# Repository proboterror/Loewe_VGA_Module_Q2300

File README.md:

# Loewe TVs Q2300 VGA Module
Recreation of VGA module PCB for Loewe TVs with Q2300 chassis.<br>
[Loewe Q2400/Q2500 Chassis VGA Module](https://github.com/proboterror/Loewe_VGA_Module_Q2500)

Project based on schematic from [Loewe Q2300 Chassis Service Manual](doc/loewe_chassis_q2300.pdf)

Schematic and PCB recreated from the scratch in KiCad and verified with Desing/Electrical Rules Checker tools.<br>

Original schematic from [Loewe Q2300 Chassis Service Manual](doc/loewe_chassis_q2300.pdf):

Recreated schematic and PCB:

VGA connector breakout board:

## Bill of materials
|Reference|Value|Footprint|Qty|
|-----|-----|-----|-----|
|C3,C5,C7|4.7u|Capacitor_SMD:CP_Elec_6.3x5.4|3|
|C4,C6,C8,C14|100n|0805|4|
|C9,C26|22n|0805|2|
|C10|1u|Capacitor_Tantalum_SMD<br>CP_EIA-3216-18_Kemet-A_Pad1.58x1.35mm_HandSolder|1|
|C13|100u|Capacitor_SMD:CP_Elec_6.3x5.7|1|
|C15,C18,C19,C20,C21,C22,C24|10p|0805|7|
|C25,C28,C29|100p|0805|3|
|J1|VGA DSUB-15|DSUB-15-HD_Male_Horizontal_P2.29x1.98mm<br>EdgePinOffset3.03mm_MountingHolesOffset4.94mm|1|
|J2|JST XH 10 pin Horizontal|JST_XH_S10B-XH-A_1x10_P2.50mm_Horizontal|1|
|L1|4u7|Inductor_SMD:1206|1|
|Q1,Q2,Q3,Q4,Q5,Q6,Q10,Q14|BC847B|SOT-23|8|
|R1,R6,R13|75R|0805|3|
|R2,R5,R7,R10,R14,R18,R19,R26,R32|47K|0805|9|
|R3,R8,R15|22K|0805|3|
|R4,R9,R17,R33,R34|100R|0805|5|
|R22|10K|0805|1|
|R25,R31,R35,R40,R43|1K|0805|5|
|U1|74HCT86|SO-14_3.9x8.65mm_P1.27mm|1|
|W2|JST XH 10 pin Vertical|JST_XH_B10B-XH-A_1x10_P2.50mm_Vertical|1|
|W3|JST XH 10 pin Vertical|JST_XH_B10B-XH-A_1x10_P2.50mm_Vertical|1|

+Cables XH 10 pin 20 + 30~50 cm, connectors: same side

## Order boards from manufacturer
Project split to 2 PCBs which should be ordered separately.
Send "gerbers\Breakout Board" and "gerbers\Main Board" folders content packed to separate zip archives.

## Build Notes
L1 inductor can be replaced with 0R resistor or solder bridge.

Pay attention on cables connectors type: same direction or reverse direction.

## Install

<https://www.youtube.com/watch?v=7eVl5yn5JIE>:<br>
Select VGA input:<br>
@djcalle1975:
> On the Q23 you have to navigate to channel 196 and if no input is detected within 10 seconds the TV will default back to the last used channel.

VGA Geometry menu:<br>
@peteagas:
> If there is no VGA menu for you on a Q23 after installation and after enabling the option byte setting, press the "i" on the Loewe remote then go to select control level then simple control level set to "No". VGA geometry will now be available to use.

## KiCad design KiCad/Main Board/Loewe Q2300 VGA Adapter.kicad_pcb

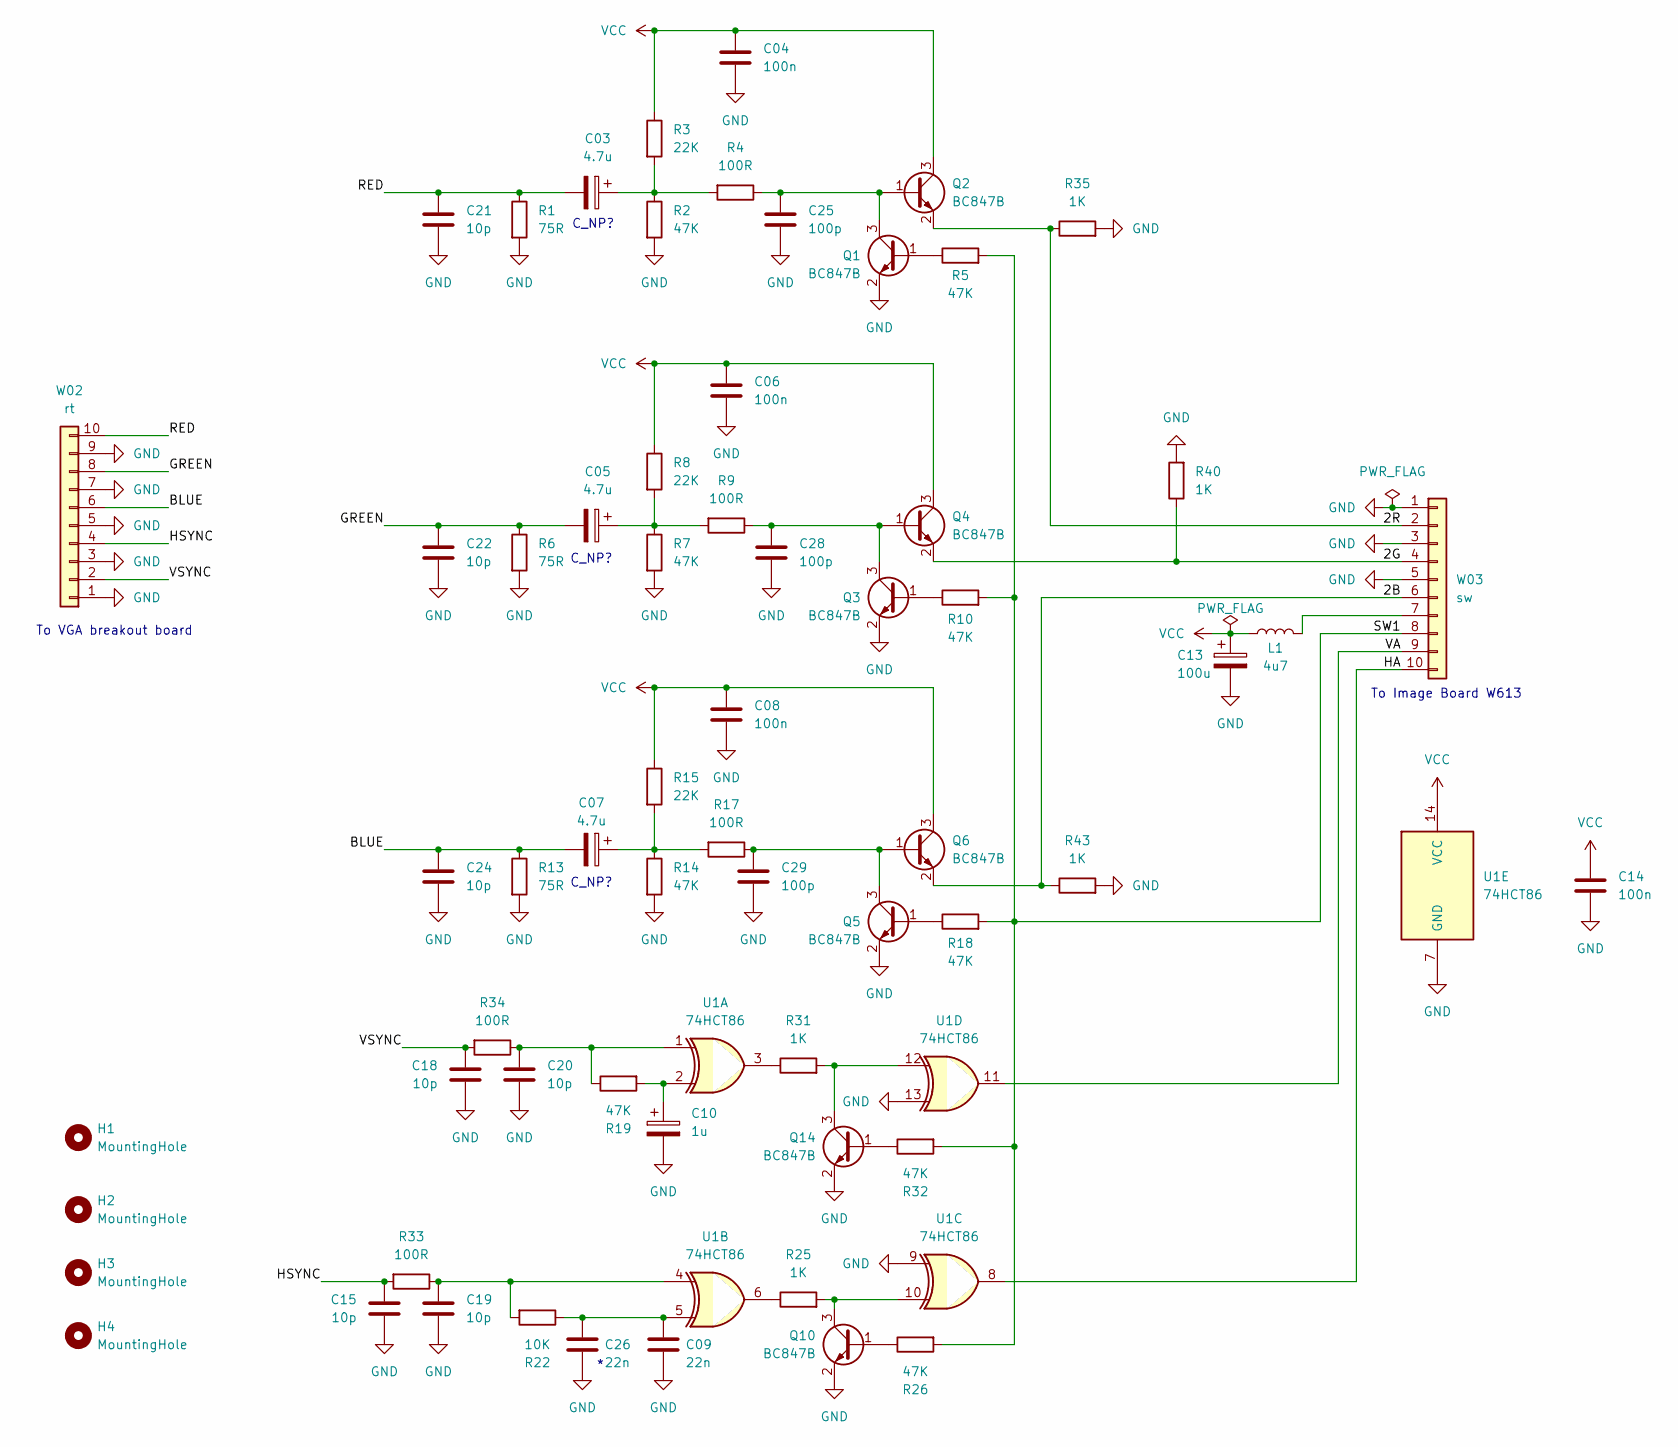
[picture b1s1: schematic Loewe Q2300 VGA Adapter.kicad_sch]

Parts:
C03, C05, C07: 4.7u; CP_Elec_4x5.4
C04, C06, C08, C14: 100n; C_0805_2012Metric_Pad1.18x1.45mm_HandSolder
C09, C26: 22n; C_0805_2012Metric_Pad1.18x1.45mm_HandSolder
C10: 1u; CP_EIA-3216-18_Kemet-A_Pad1.58x1.35mm_HandSolder
C13: 100u; CP_Elec_6.3x5.7
C15, C18, C19, C20, C21, C22, C24: 10p; C_0805_2012Metric_Pad1.18x1.45mm_HandSolder
C25, C28, C29: 100p; C_0805_2012Metric_Pad1.18x1.45mm_HandSolder
H1, H2, H3, H4: MountingHole; MountingHole_3.2mm_M3_Pad
L1: 4u7; L_1210_3225Metric_Pad1.42x2.65mm_HandSolder
Q1, Q2, Q3, Q4, Q5, Q6, Q10, Q14: BC847B; SOT-23
R1, R6, R13: 75R; R_0805_2012Metric_Pad1.20x1.40mm_HandSolder
R2, R5, R7, R10, R14, R18, R19, R26, R32: 47K; R_0805_2012Metric_Pad1.20x1.40mm_HandSolder
R3, R8, R15: 22K; R_0805_2012Metric_Pad1.20x1.40mm_HandSolder
R4, R9, R17, R33, R34: 100R; R_0805_2012Metric_Pad1.20x1.40mm_HandSolder
R22: 10K; R_0805_2012Metric_Pad1.20x1.40mm_HandSolder
R25, R31, R35, R40, R43: 1K; R_0805_2012Metric_Pad1.20x1.40mm_HandSolder
U1: 74HCT86; SO-14_3.9x8.65mm_P1.27mm
W02: rt; JST_XH_B10B-XH-A_1x10_P2.54mm_Vertical
W03: sw; JST_XH_B10B-XH-A_1x10_P2.54mm_Vertical

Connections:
/2B: Q6.2 (E), R43.1, W03.6
/2G: Q4.2 (E), R40.1, W03.4
/2R: Q2.2 (E), R35.1, W03.2
/BLUE: C07.2, C24.1, R13.1, W02.6
/GREEN: C05.2, C22.1, R6.1, W02.8
/HA: U1.8, W03.10
/HSYNC: C15.2, R33.2, W02.4
/RED: C03.2, C21.1, R1.1, W02.10
/SW1: R5.2, R10.2, R18.2, R26.2, R32.2, W03.8
/VA: U1.11, W03.9
/VSYNC: C18.1, R34.2, W02.2
GND: C04.2, C06.2, C08.2, C09.1, C10.2, C13.2, C14.2, C15.1, C18.2, C19.1, C20.1, C21.2, C22.2, C24.2, C25.2, C26.1, C28.2, C29.2, Q1.2 (E), Q3.2 (E), Q5.2 (E), Q10.2 (E), Q14.2 (E), R1.2, R2.2, R6.2, R7.2, R13.2, R14.2, R35.2, R40.2, R43.2, U1.7 (GND), U1.9, U1.13, W02.1, W02.3, W02.5, W02.7, W02.9, W03.1, W03.3, W03.5
unnamed: C03.1, R2.1, R3.2, R4.2
unnamed: C05.1, R7.1, R8.2, R9.2
unnamed: C07.1, R14.1, R15.2, R17.2
unnamed: C09.2, C26.2, R22.1, U1.5
unnamed: C10.1, R19.2, U1.2
unnamed: C19.2, R22.2, R33.1, U1.4
unnamed: C20.2, R19.1, R34.1, U1.1
unnamed: Q1.1 (B), R5.1
unnamed: C25.1, Q1.3 (C), Q2.1 (B), R4.1
unnamed: Q3.1 (B), R10.1
unnamed: C28.1, Q3.3 (C), Q4.1 (B), R9.1
unnamed: Q5.1 (B), R18.1
unnamed: C29.1, Q5.3 (C), Q6.1 (B), R17.1
unnamed: Q10.1 (B), R26.1
unnamed: Q10.3 (C), R25.2, U1.10
unnamed: Q14.1 (B), R32.1
unnamed: Q14.3 (C), R31.2, U1.12
unnamed: R25.1, U1.6
unnamed: R31.1, U1.3
unnamed: L1.2, W03.7
VCC: C04.1, C06.1, C08.1, C13.1, C14.1, L1.1, Q2.3 (C), Q4.3 (C), Q6.3 (C), R3.1, R8.1, R15.1, U1.14 (VCC)

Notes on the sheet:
To VGA breakout board
C_NP?
To Image Board W613

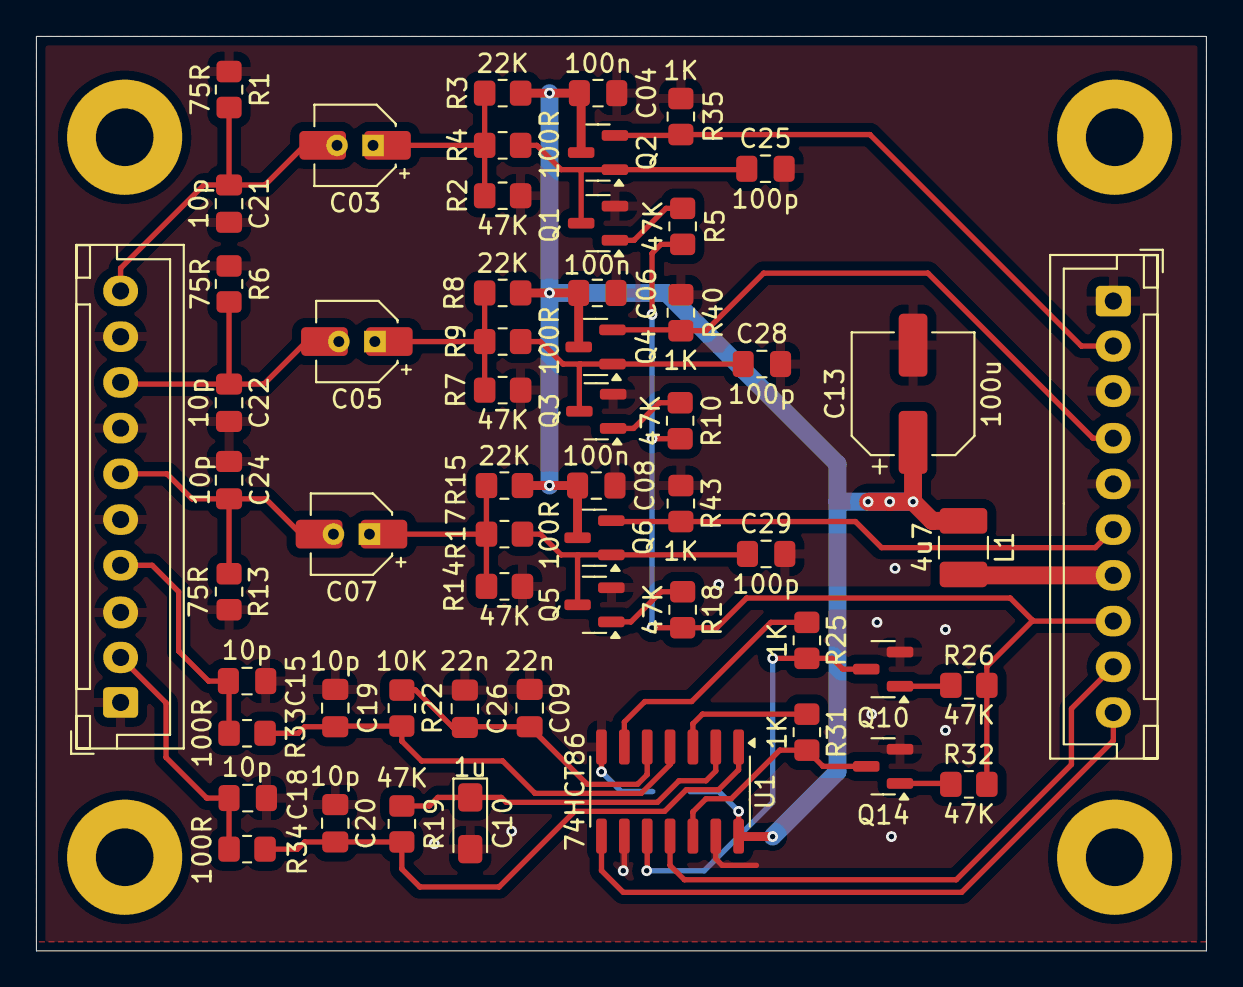
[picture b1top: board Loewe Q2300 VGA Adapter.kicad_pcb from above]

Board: 2 copper layers, 65.0 x 50.8 mm, 63 parts (1 on the bottom side), 33 nets.

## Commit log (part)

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2025-11-14 Initial schematic and PCB. Project description.
2025-11-14 Update README.md.
2025-11-14 Change L1 inductor footprint to 1210 (TDK/EPCOS NLCV32T-4R7M-EF).
2025-11-14 Change RGB input capacitors footprints to Capacitor_SMD:CP_Elec_4x5.4. Reverse RGB capacitors polarity.
2025-11-16 Move components values from *.Fab layer to *.SilkS. Align mounting holes positions to 55/40 mm.
2025-11-22 Add non-standard 2.54 mm JST XH S10B connectors footprints based on KiCad 2.50 mm ones.
2025-11-22 Replace JST XH 2.50 mm with custom 2.54 mm.
2025-11-22 Edit PCB dimensions drawing.
2025-11-22 Replace footprint for RGB input capacitors with custom combined SMD/THT one.
2025-11-22 Add version to PCB silkscreen.
2025-11-22 Production V.1.0 gerbers.
2025-12-14 KiCad projects update paths.
2025-12-14 Replace incorrect Connector_Dsub:DSUB-15-HD_Male with Connector_Dsub:DSUB-15-HD_Female.
2025-12-14 Update gerbers.
